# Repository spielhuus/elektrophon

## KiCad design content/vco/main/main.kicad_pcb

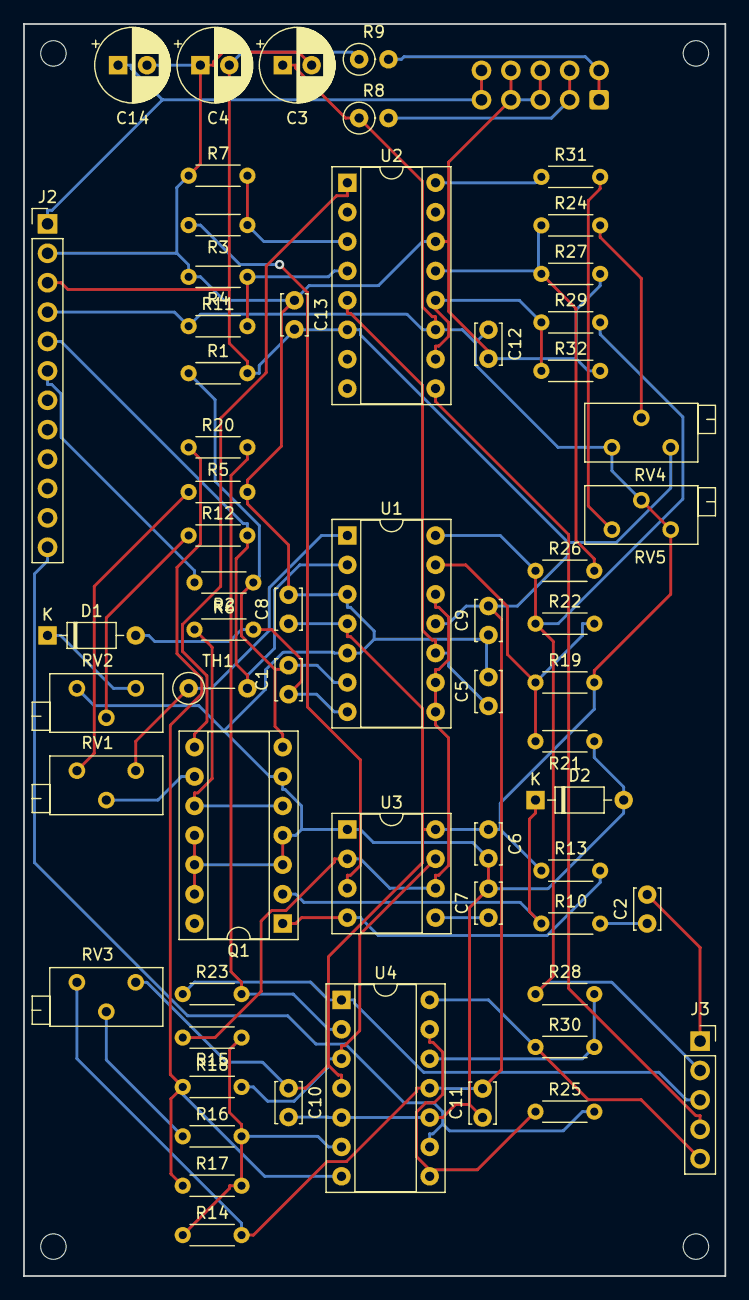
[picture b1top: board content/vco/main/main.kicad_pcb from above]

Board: 2 copper layers, 60.6 x 108.2 mm, 66 parts (1 on the bottom side), 45 nets.

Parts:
C1: 100p; C_Disc_D3.4mm_W2.1mm_P2.50mm
C2: 470p; C_Disc_D3.4mm_W2.1mm_P2.50mm
C3, C4, C14: 22u; CP_Radial_D6.3mm_P2.50mm
C5: 2200p; C_Disc_D3.4mm_W2.1mm_P2.50mm
C6, C8, C9, C10, C11, C12, C13: 0.1u; C_Disc_D3.4mm_W2.1mm_P2.50mm
C7: 0.001u; C_Disc_D3.4mm_W2.1mm_P2.50mm
D1, D2: 1N4148; D_DO-35_SOD27_P7.62mm_Horizontal
H1, H2, H3, H4: MountingHole; MountingHole_2.2mm_M2
J1: IDC Header; IDC-Header_2x05_P2.54mm_Vertical
J2: Conn_01x12_Female; PinHeader_1x12_P2.54mm_Vertical
J3: Conn_01x05_Female; PinSocket_1x05_P2.54mm_Vertical
Q1: THAT340; DIP-14_W7.62mm_Socket
R1: 1M5; R_Axial_DIN0204_L3.6mm_D1.6mm_P5.08mm_Horizontal
R2, R12, R16, R24: 1M; R_Axial_DIN0204_L3.6mm_D1.6mm_P5.08mm_Horizontal
R3, R13: 4k7; R_Axial_DIN0204_L3.6mm_D1.6mm_P5.08mm_Horizontal
R4, R7: 1k5; R_Axial_DIN0204_L3.6mm_D1.6mm_P5.08mm_Horizontal
R5, R27: 390; R_Axial_DIN0204_L3.6mm_D1.6mm_P5.08mm_Horizontal
R6: 22k; R_Axial_DIN0204_L3.6mm_D1.6mm_P5.08mm_Horizontal
R8, R9: 10; R_Axial_DIN0207_L6.3mm_D2.5mm_P2.54mm_Vertical
R10, R15, R17, R26: 100k; R_Axial_DIN0204_L3.6mm_D1.6mm_P5.08mm_Horizontal
R11, R18, R19, R20, R23: 10k; R_Axial_DIN0204_L3.6mm_D1.6mm_P5.08mm_Horizontal
R14: 150k; R_Axial_DIN0204_L3.6mm_D1.6mm_P5.08mm_Horizontal
R21, R22: 20k; R_Axial_DIN0204_L3.6mm_D1.6mm_P5.08mm_Horizontal
R25: 120k; R_Axial_DIN0204_L3.6mm_D1.6mm_P5.08mm_Horizontal
R28: 2k2; R_Axial_DIN0204_L3.6mm_D1.6mm_P5.08mm_Horizontal
R29, R31: 39k; R_Axial_DIN0204_L3.6mm_D1.6mm_P5.08mm_Horizontal
R30: 2M2; R_Axial_DIN0204_L3.6mm_D1.6mm_P5.08mm_Horizontal
R32: 300k; R_Axial_DIN0204_L3.6mm_D1.6mm_P5.08mm_Horizontal
RV1: 100; Potentiometer_Bourns_3296Z_Horizontal
RV2, RV3, RV4: 100k; Potentiometer_Bourns_3296Z_Horizontal
RV5: 25k; Potentiometer_Bourns_3296Z_Horizontal
TH1: 2k +3500ppm/°C; R_Axial_DIN0207_L6.3mm_D2.5mm_P5.08mm_Vertical
U1, U4: TL074; DIP-14_W7.62mm_Socket
U2: LM13700; DIP-16_W7.62mm_Socket
U3: TLC555xP; DIP-8_W7.62mm_Socket

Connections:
+5V: C14.1, J1.9, J1.10, J2.1
+15V: C3.1, C6.1, C8.1, C10.1, C12.1, J2.4, R8.1, R11.1, R13.1, R19.2, RV3.1, RV4.1, RV5.2, RV5.3, U1.4, U2.11, U3.8, U4.4
-15V: C4.2, C9.2, C11.2, C13.2, J2.3, R1.2, R9.1, R14.2, RV3.3, RV4.3, U1.11, U2.6, U4.11
/exp_fm: J2.5, R12.2, TH1.2, U1.2
/lin_fm: J2.6, R2.2
/net_q: R3.2, U3.3
/pulse: J3.5, R30.1, U4.14
/pwm_cv: J2.12, R25.2, U4.9
/ramp: J3.3, R23.1, U4.1
/sine: J3.4, U2.9
/sync: C2.2, J3.1
/triangle: J3.2, R22.1, R26.1, R28.1, R29.2, U1.14
GND: C3.2, C4.1, C5.2, C6.2, C7.2, C8.2, C9.1, C10.2, C11.1, C12.2, C13.1, C14.2, D2.2, J1.5, J1.6, J1.7, J1.8, J2.2, Q1.3, Q1.4, Q1.6, Q1.11, Q1.12, Q1.13, R4.2, R5.2, R7.1, R21.1, R27.2, R32.2, RV2.3, U1.3, U1.5, U2.14, U3.1, U4.5, U4.10
unnamed: C1.1, D1.2, R6.2, U1.7
unnamed: C1.2, Q1.7, R1.1, R2.1, U1.6
unnamed: C2.1, R10.2
unnamed: C5.1, U1.10, U2.5
unnamed: C7.1, U3.5
unnamed: D1.1, RV2.1
unnamed: D2.1, Q1.2, R10.1
unnamed: Q1.1, R13.2, U3.4
unnamed: Q1.8, U2.1
unnamed: Q1.9, RV1.2
unnamed: Q1.5, Q1.10, R6.1
unnamed: R3.1, R7.2, U2.3
unnamed: R5.1, RV1.3
unnamed: R4.1, R11.2, U2.4
unnamed: R12.1, RV2.2
unnamed: R14.1, R15.1, R16.2, R17.2, U4.6
unnamed: R15.2, U1.8, U1.9, U1.12, U3.2, U3.6
unnamed: R16.1, RV3.2
unnamed: R17.1, R18.1, R20.1, U4.7
unnamed: R18.2, U3.7, U4.3
unnamed: R19.1, R21.2, R22.2, U1.13
unnamed: R20.2, R23.2, U4.2
unnamed: R24.1, R26.2, R27.1, U2.13
unnamed: R24.2, RV4.2
unnamed: R25.1, U4.8, U4.13
unnamed: R28.2, R30.2, U4.12
unnamed: R29.1, R32.1, U2.10, U2.12
unnamed: R31.1, U2.16
unnamed: R31.2, RV5.1
unnamed: RV1.1, TH1.1, U1.1
VN: J1.1, J1.2, R9.2
VP: J1.3, J1.4, R8.2

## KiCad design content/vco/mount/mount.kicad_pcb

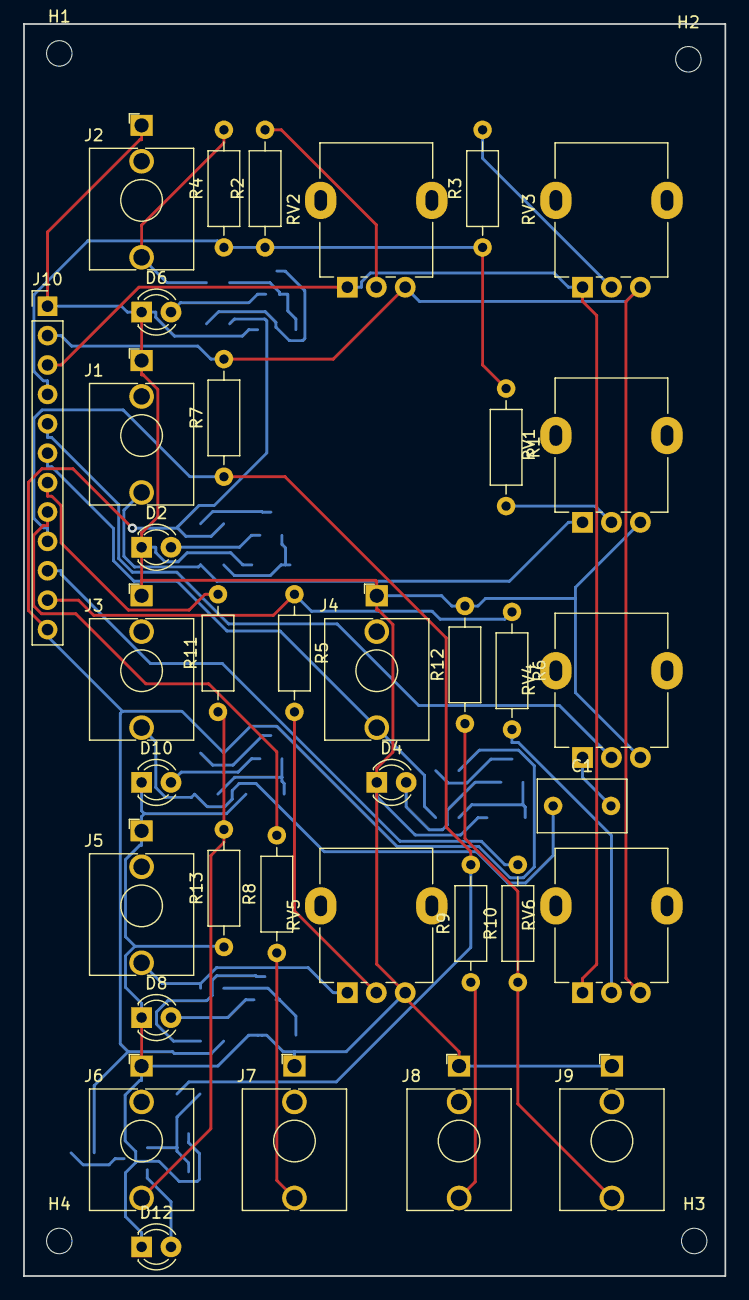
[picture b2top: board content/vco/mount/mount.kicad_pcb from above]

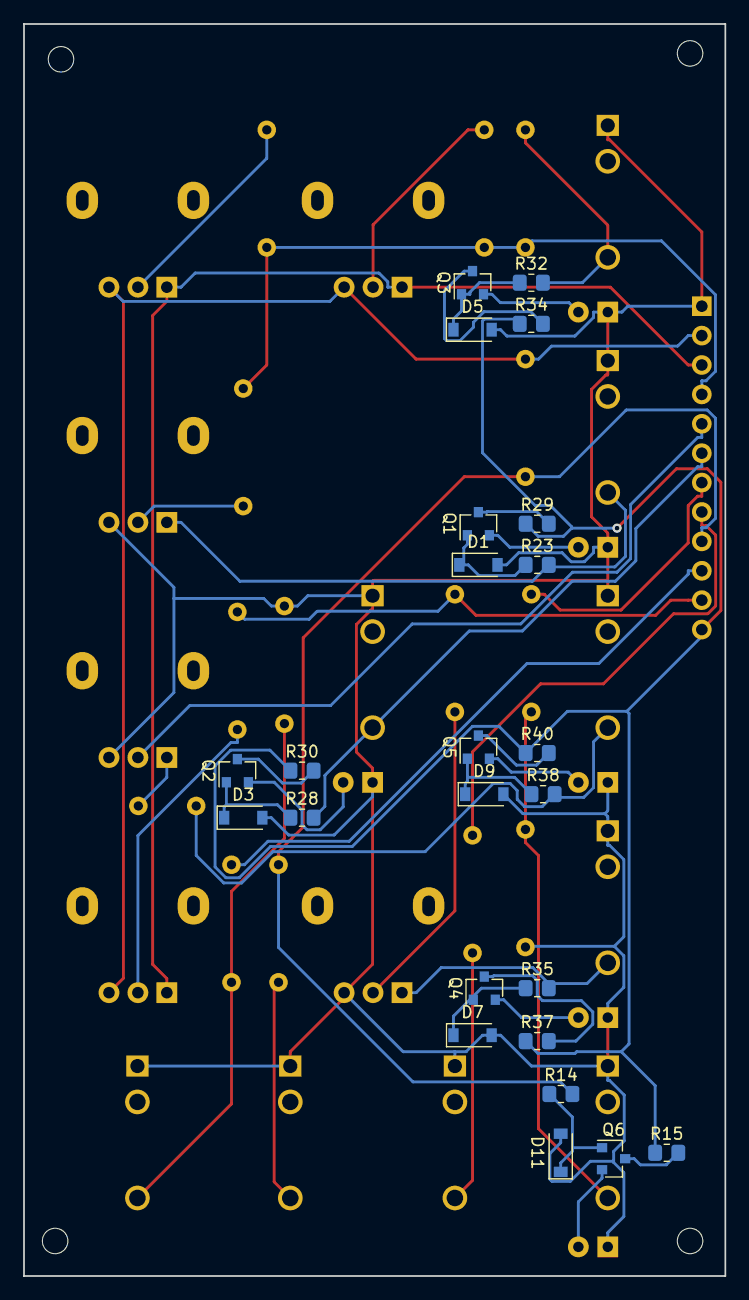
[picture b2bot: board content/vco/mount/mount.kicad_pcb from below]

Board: 2 copper layers, 60.6 x 108.2 mm, 64 parts (24 on the bottom side), 44 nets.

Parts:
C1: 0.22u; C_Disc_D7.5mm_W4.4mm_P5.00mm
D1, D3, D5, D7, D9, D11: 1N4148W; D_SOD-123
D2, D4, D6, D8, D10, D12: LED; LED_D3.0mm
H1, H2, H3, H4: MountingHole; MountingHole_2.2mm_M2
J1: exp.fm; Jack_3.5mm_WQP-PJ398SM_Vertical
J2: 1v/oct; Jack_3.5mm_WQP-PJ398SM_Vertical
J3: lin.fm; Jack_3.5mm_WQP-PJ398SM_Vertical
J4: sync; Jack_3.5mm_WQP-PJ398SM_Vertical
J5: pwm; Jack_3.5mm_WQP-PJ398SM_Vertical
J6, J7, J8, J9: AudioJack2_SwitchT; Jack_3.5mm_WQP-PJ398SM_Vertical
J10: Conn_01x12_Male; PinHeader_1x12_P2.54mm_Vertical
Q1, Q2, Q3, Q4, Q5, Q6: MMBT3904; SOT-23
R1, R2, R4, R5: 100k; R_Axial_DIN0207_L6.3mm_D2.5mm_P10.16mm_Horizontal
R3: 3M3; R_Axial_DIN0207_L6.3mm_D2.5mm_P10.16mm_Horizontal
R6: 330k; R_Axial_DIN0207_L6.3mm_D2.5mm_P10.16mm_Horizontal
R7: 5k6; R_Axial_DIN0207_L6.3mm_D2.5mm_P10.16mm_Horizontal
R8, R9: 1k; R_Axial_DIN0207_L6.3mm_D2.5mm_P10.16mm_Horizontal
R10: 3k; R_Axial_DIN0207_L6.3mm_D2.5mm_P10.16mm_Horizontal
R11, R13: 2k; R_Axial_DIN0207_L6.3mm_D2.5mm_P10.16mm_Horizontal
R12: 1k8; R_Axial_DIN0207_L6.3mm_D2.5mm_P10.16mm_Horizontal
R14, R23, R28, R32, R35, R38: 100k; R_0805_2012Metric_Pad1.20x1.40mm_HandSolder
R15, R30, R37: 5k; R_0805_2012Metric_Pad1.20x1.40mm_HandSolder
R29, R34, R40: 5.1k; R_0805_2012Metric_Pad1.20x1.40mm_HandSolder
RV1, RV2, RV3, RV4, RV5, RV6: 100k; Potentiometer_Alpha_RD901F-40-00D_Single_Vertical

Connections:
+5V: J10.12, R15.1, R29.1, R30.1, R34.1, R37.1, R40.1
+15V: J10.3, RV2.1, RV3.1, RV6.1
-15V: J10.2, R7.2, RV2.3, RV3.3, RV6.3
/exp.fm: J1.T, R23.2, RV1.1
/exp_fm: J10.4, R1.1, R2.1, R3.1, R4.1
/lin.fm: C1.1, J3.T, R38.2
/lin_fm: J10.5, RV4.2
/pulse: J10.10, R10.2
/pwm: J5.T, R35.2, RV5.1
/pwm_cv: J10.11, R5.1, R6.1
/ramp: J10.8, R8.2
/sine: J10.9, R7.1, R9.2, R14.2
/sync: J4.T, J10.6, R28.2
/triangle: J10.7, R11.2
/v_oct: J2.T, R4.2, R32.2
GND: D1.2, D2.1, D3.2, D4.1, D5.2, D6.1, D7.2, D8.1, D9.2, D10.1, D11.2, D12.1, J1.S, J2.S, J3.S, J4.S, J5.S, J6.S, J7.S, J8.S, J9.S, J10.1, R12.2, R13.1, RV1.3, RV4.3, RV5.3
unnamed: C1.2, RV4.1
unnamed: D1.1, Q1.1, R23.1
unnamed: D2.2, Q1.2
unnamed: D3.1, Q2.1, R28.1
unnamed: D4.2, Q2.2
unnamed: D5.1, Q3.1, R32.1
unnamed: D6.2, Q3.2
unnamed: D7.1, Q4.1, R35.1
unnamed: D8.2, Q4.2
unnamed: D9.1, Q5.1, R38.1
unnamed: D10.2, Q5.2
unnamed: D11.1, Q6.1, R14.1
unnamed: D12.2, Q6.2
unnamed: J6.T, R11.1, R13.2
unnamed: J7.T, R8.1
unnamed: J8.T, R9.1
unnamed: J9.T, R10.1, R12.1
unnamed: Q1.3, R29.2
unnamed: Q2.3, R30.2
unnamed: Q3.3, R34.2
unnamed: Q4.3, R37.2
unnamed: Q5.3, R40.2
unnamed: Q6.3, R15.2
unnamed: R1.2, RV1.2
unnamed: R2.2, RV2.2
unnamed: R3.2, RV3.2
unnamed: R5.2, RV5.2
unnamed: R6.2, RV6.2

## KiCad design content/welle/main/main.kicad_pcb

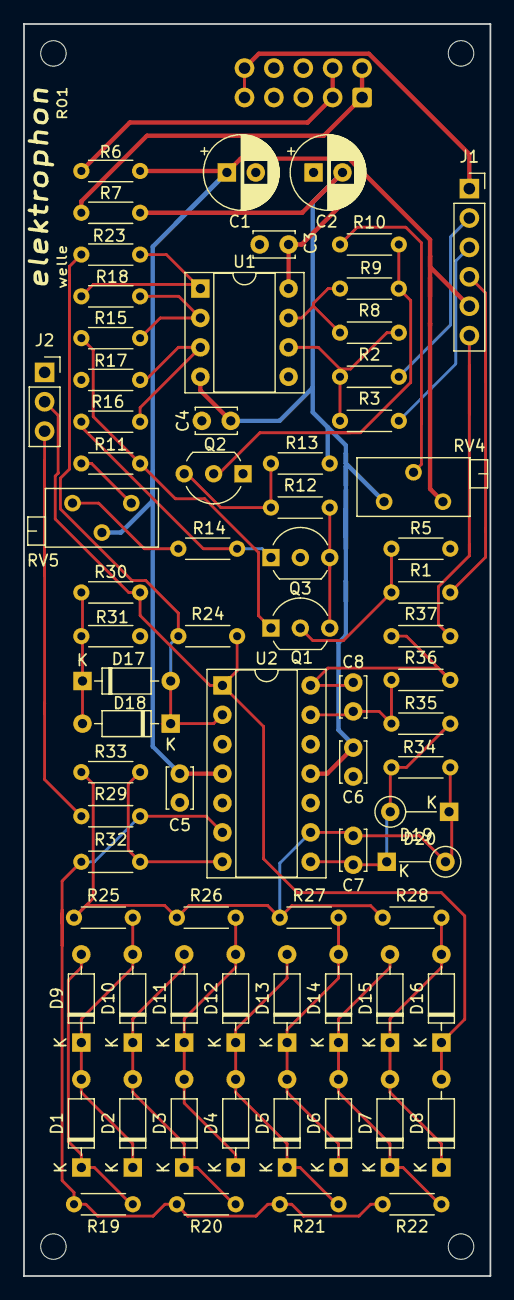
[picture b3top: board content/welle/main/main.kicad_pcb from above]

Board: 2 copper layers, 40.3 x 108.2 mm, 78 parts (1 on the bottom side), 42 nets.

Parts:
C1, C2: 22u; CP_Radial_D6.3mm_P2.50mm
C3, C4, C5, C6: 0.1u; C_Disc_D3.4mm_W2.1mm_P2.50mm
C7, C8: 10p*; C_Disc_D3.4mm_W2.1mm_P2.50mm
D1, D2, D3, D4, D5, D6, D7, D8, D9, D10, D11, D12, D13, D14, D15, D16, D17, D18: D; D_DO-35_SOD27_P7.62mm_Horizontal
D19, D20: D; D_DO-35_SOD27_P5.08mm_Vertical_KathodeUp
H1, H2, H3, H4: MountingHole; MountingHole_2.2mm_M2
J1: Conn_01x06_Female; PinSocket_1x06_P2.54mm_Vertical
J2: Conn_01x03_Female; PinSocket_1x03_P2.54mm_Vertical
J4: 10 Pos; IDC-Header_2x05_P2.54mm_Vertical
Q1, Q2, Q3: BC547; TO-92_Inline_Wide
R1, R3, R8, R17, R18, R23, R24: 100k; R_Axial_DIN0204_L3.6mm_D1.6mm_P5.08mm_Horizontal
R2: 68k; R_Axial_DIN0204_L3.6mm_D1.6mm_P5.08mm_Horizontal
R5: 680; R_Axial_DIN0204_L3.6mm_D1.6mm_P5.08mm_Horizontal
R6, R7: 10; R_Axial_DIN0204_L3.6mm_D1.6mm_P5.08mm_Horizontal
R9, R10: 22k; R_Axial_DIN0204_L3.6mm_D1.6mm_P5.08mm_Horizontal
R11, R13, R14, R19, R20, R21, R22, R25, R26, R27, R28: 15k; R_Axial_DIN0204_L3.6mm_D1.6mm_P5.08mm_Horizontal
R12, R30: 33k; R_Axial_DIN0204_L3.6mm_D1.6mm_P5.08mm_Horizontal
R15, R16: 10k; R_Axial_DIN0204_L3.6mm_D1.6mm_P5.08mm_Horizontal
R29: 27k; R_Axial_DIN0204_L3.6mm_D1.6mm_P5.08mm_Horizontal
R31: 2k7; R_Axial_DIN0204_L3.6mm_D1.6mm_P5.08mm_Horizontal
R32, R33: 5k6; R_Axial_DIN0204_L3.6mm_D1.6mm_P5.08mm_Horizontal
R34, R36: 56k; R_Axial_DIN0204_L3.6mm_D1.6mm_P5.08mm_Horizontal
R35: 6k8; R_Axial_DIN0204_L3.6mm_D1.6mm_P5.08mm_Horizontal
R37: 470; R_Axial_DIN0204_L3.6mm_D1.6mm_P5.08mm_Horizontal
RV4: 50k; Potentiometer_Bourns_3296Z_Horizontal
RV5: 1k; Potentiometer_Bourns_3296Z_Horizontal
U1: TL072; DIP-8_W7.62mm_Socket
U2: TL074; DIP-14_W7.62mm_Socket

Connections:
+5V: J1.1, J4.9, J4.10
+15V: C1.1, C3.1, C5.1, J1.5, R6.1, RV4.3, RV5.2, U1.8, U2.4
-15V: C2.2, C4.2, C6.2, R7.1, R13.1, RV4.1, U1.4, U2.11
/control: J1.2, R2.2
/input: J1.4, R1.2
/out: J1.6, R37.2
/range: J1.3, R3.2
/shape_a: D8.2, D16.1, J2.2, R24.2, R30.1, U2.1
/shape_b: J2.3, R29.1
GND: C1.2, C2.1, C3.2, C4.1, C5.2, C6.1, J2.1, J4.5, J4.6, J4.7, J4.8, Q2.1, Q3.2, R5.1, R17.1, R31.1, U1.5, U2.3, U2.5, U2.10, U2.12
unnamed: C7.1, D19.1, D20.2, R34.2, R35.1, U2.8
unnamed: C7.2, D19.2, D20.1, R25.1, R26.1, R27.1, R28.1, R33.2, R34.1, U2.9
unnamed: C8.1, R36.2, R37.1, U2.14
unnamed: C8.2, R35.2, R36.1, U2.13
unnamed: D1.1, D9.2, R19.1
unnamed: D1.2, D2.1, D9.1, D10.2, R25.2
unnamed: D2.2, D3.1, D10.1, D11.2, R20.1
unnamed: D3.2, D4.1, D11.1, D12.2, R26.2
unnamed: D4.2, D5.1, D12.1, D13.2, R21.1
unnamed: D5.2, D6.1, D13.1, D14.2, R27.2
unnamed: D6.2, D7.1, D14.1, D15.2, R22.1
unnamed: D7.2, D8.1, D15.1, D16.2, R28.2
unnamed: D17.1, D18.2, R30.2, R31.2
unnamed: D17.2, D18.1, R23.2, R24.1, U2.2
unnamed: Q1.1, R11.1, R15.2
unnamed: Q1.2, R1.1, R5.2
unnamed: Q1.3, Q3.3, R12.2
unnamed: Q2.2, R9.1, R10.2
unnamed: Q2.3, R12.1, R13.2
unnamed: Q3.1, R14.1, R16.2
unnamed: R2.1, R3.1, R8.2, U1.6
unnamed: R8.1, R9.2, U1.7
unnamed: R10.1, RV4.2
unnamed: R11.2, RV5.1
unnamed: R14.2, RV5.3
unnamed: R15.1, R18.1, U1.2
unnamed: R16.1, R17.2, U1.3
unnamed: R18.2, R23.1, U1.1
unnamed: R19.2, R20.2, R21.2, R22.2, R29.2, R32.1, U2.6
unnamed: R32.2, R33.1, U2.7
VN: J4.1, J4.2, R7.2
VP: J4.3, J4.4, R6.2

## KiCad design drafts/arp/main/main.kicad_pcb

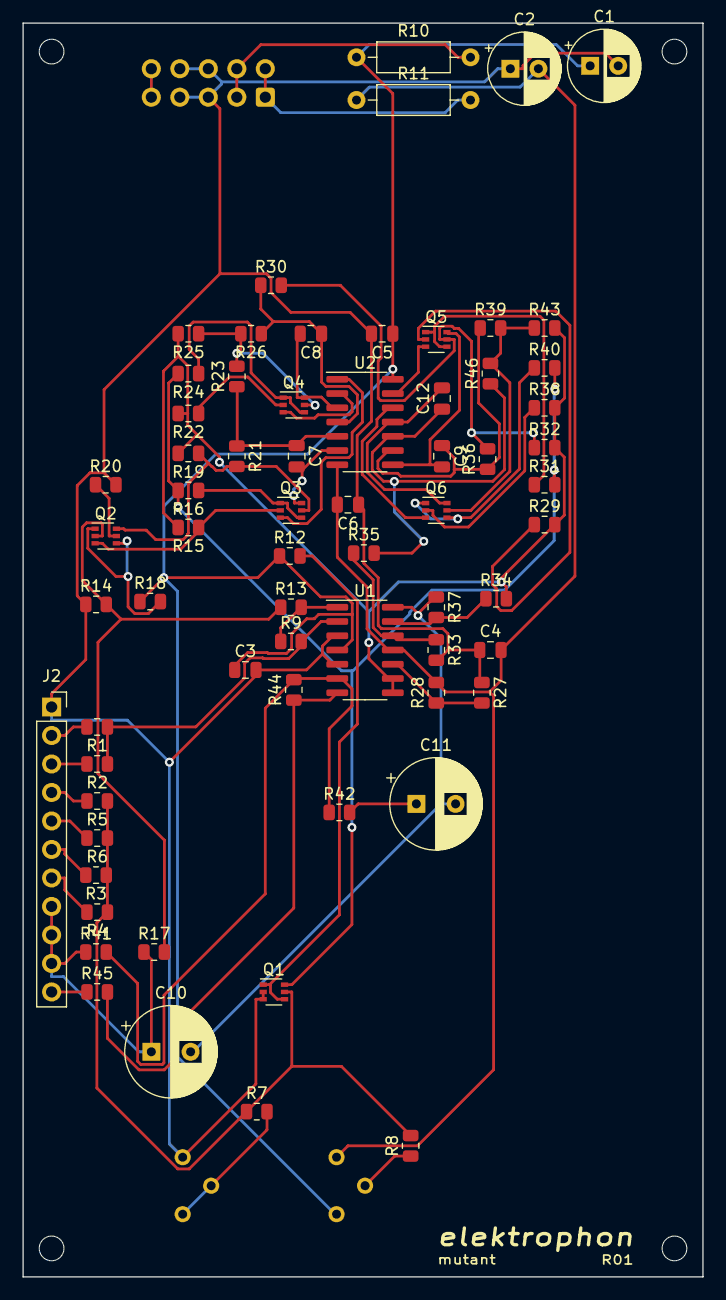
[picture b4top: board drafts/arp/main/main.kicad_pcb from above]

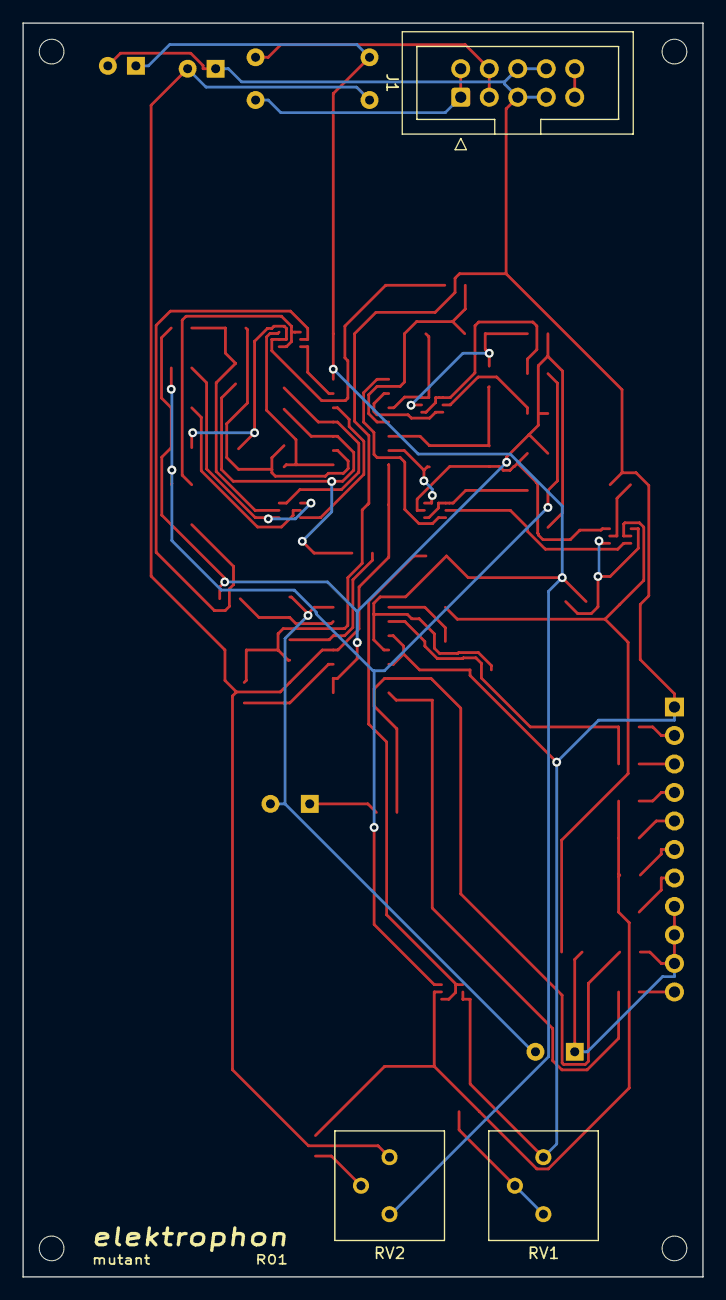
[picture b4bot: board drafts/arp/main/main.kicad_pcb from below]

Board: 2 copper layers, 60.6 x 111.8 mm, 74 parts (3 on the bottom side), 56 nets.

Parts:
C1, C2: 22u; CP_Radial_D6.3mm_P2.50mm
C3, C4, C5, C6: 0.1u; C_0805_2012Metric
C7, C8, C9, C12: 470p; C_0805_2012Metric
C10, C11: 22u; CP_Radial_D8.0mm_P3.50mm
J1: IDC Header; IDC-Header_2x05_P2.54mm_Vertical
J2: Conn_01x11_Female; PinSocket_1x11_P2.54mm_Vertical
Q1, Q2, Q3, Q4, Q5, Q6: MMDT3906; SOT-363_SC-70-6
R1, R2, R4, R5, R6, R8, R9, R13, R33: 100k; R_0805_2012Metric
R3: 150k; R_0805_2012Metric
R7, R14, R16, R24, R31, R40, R45: 1k; R_0805_2012Metric
R10, R11: 10; R_Axial_DIN0207_L6.3mm_D2.5mm_P10.16mm_Horizontal
R12, R21, R23, R26, R27, R28, R30, R34, R35, R36, R37, R39, R46: 10k; R_0805_2012Metric
R15, R19, R20, R22, R25, R29, R32, R38, R43: 220; R_0805_2012Metric
R17: 15k; R_0805_2012Metric
R18: 33k; R_0805_2012Metric
R41: 22k; R_0805_2012Metric
R42, R44: 56k; R_0805_2012Metric
REF1, REF2, REF3, REF4: MountingHole_2.2mm_M2
RV1: 2.2k; Potentiometer_Bourns_3386P_Vertical
RV2: 47k; Potentiometer_Bourns_3386P_Vertical
U1: TL074; SOIC-14_3.9x8.7mm_P1.27mm
U2: LM3900; SOIC-14_3.9x8.7mm_P1.27mm

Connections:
+5V: J1.9, J1.10
+15V: C1.1, C3.1, C5.1, R10.1, R12.1, R18.1, RV2.3, U1.4, U2.14
-15V: C2.2, C4.2, C6.2, R11.1, R28.2, RV2.1, U1.11, U2.7
CV1: J2.4, R5.2
CV2: J2.5, R6.2
FREQ: J2.6, R3.2
GND: C1.2, C2.1, C3.2, C4.1, C5.2, C6.1, J1.5, J1.6, J1.7, J1.8, J2.1, Q1.2, Q1.3, R14.1, R20.2, R27.1, R33.2, RV1.1, U1.3, U1.5
IN1: J2.2, R1.2
IN2: J2.3, R2.2
unnamed: C7.1, R21.1, R23.1, U2.5
unnamed: C7.2, Q3.6, U2.6
unnamed: C8.1, R26.1, R30.1, U2.4
unnamed: C8.2, Q4.6, U2.3
unnamed: C9.1, R36.1, R39.1, U2.9
unnamed: C9.2, Q5.6, U2.8
unnamed: C10.2, C11.2, R37.1, U1.14
unnamed: C11.1, R42.2
unnamed: C12.1, R35.2, R46.1, U2.10
unnamed: C12.2, Q6.6, U2.11
unnamed: Q1.1, Q1.4, R12.2
unnamed: Q1.5, R3.1, R4.1, R5.1, R6.1, R7.1, R8.2
unnamed: Q1.6, R16.2, R24.2, R31.2, R40.2
unnamed: Q2.1, Q2.4, R18.2
unnamed: Q2.2, R13.1, R14.2, R17.2
unnamed: Q2.3, Q3.2, R15.1
unnamed: Q2.5, R20.1
unnamed: Q2.6, Q3.5, R19.1, R21.2
unnamed: Q3.1, Q3.4, R16.1
unnamed: Q3.3, U2.1
unnamed: Q4.1, Q4.4, R24.1
unnamed: Q4.2, R22.1
unnamed: Q4.3, U2.2
unnamed: Q4.5, R23.2, R25.1, R26.2
unnamed: Q5.1, Q5.4, R31.1
unnamed: Q5.2, R29.1
unnamed: Q5.3, U2.13
unnamed: Q5.5, R30.2, R32.1, R36.2
unnamed: Q6.1, Q6.4, R40.1
unnamed: Q6.2, R38.1
unnamed: Q6.3, U2.12
unnamed: Q6.5, R39.2, R43.1, R46.2
unnamed: R1.1, R2.1, R9.2, U1.2
unnamed: R7.2, RV1.2, RV1.3
unnamed: R8.1, RV2.2
unnamed: R9.1, R13.2, U1.1
unnamed: R15.2, R19.2, R22.2, R25.2, R29.2, R32.2, R34.2, R38.2, R43.2, U1.8, U1.9
unnamed: R27.2, R28.1, U1.10
unnamed: R33.1, R35.1, U1.12
unnamed: R34.1, R37.2, U1.13
unnamed: R41.2, R42.1, R44.2, U1.6
unnamed: R44.1, R45.2, U1.7
OUT: J2.11, R45.1
RES_A: C10.1, J2.8, J2.9, J2.10, R17.1, R41.1
VN: J1.1, J1.2, R11.2
VP: J1.3, J1.4, R10.2
V_OCT: J2.7, R4.2

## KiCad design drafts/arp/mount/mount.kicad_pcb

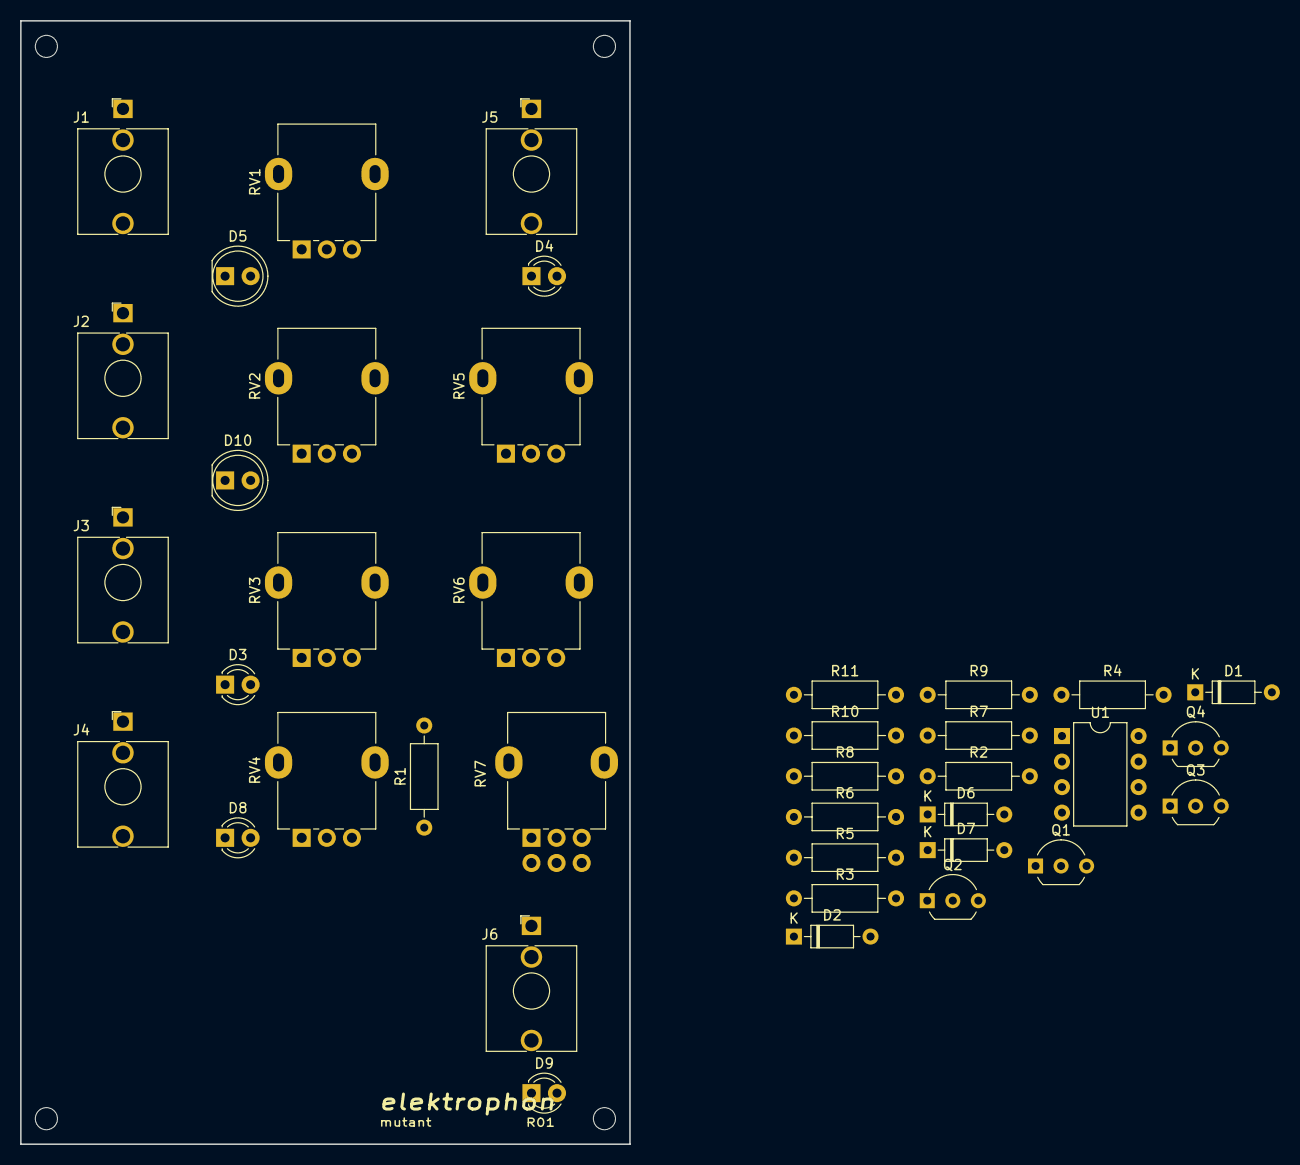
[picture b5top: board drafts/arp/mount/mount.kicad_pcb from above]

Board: 2 copper layers, 60.6 x 111.8 mm, 43 parts (0 on the bottom side), 31 nets, no tracks yet.

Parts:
D1, D2, D6, D7: 1N4148; D_DO-35_SOD27_P7.62mm_Horizontal
D3, D4, D8, D9: WP710A10L; LED_D3.0mm
D5, D10: LED_Dual_2pin; LED_D5.0mm
J1: CV1; Jack_3.5mm_WQP-PJ398SM_Vertical
J2: CV2; Jack_3.5mm_WQP-PJ398SM_Vertical
J3: IN1; Jack_3.5mm_WQP-PJ398SM_Vertical
J4: IN2; Jack_3.5mm_WQP-PJ398SM_Vertical
J5: V/OCT; Jack_3.5mm_WQP-PJ398SM_Vertical
J6: OUT; Jack_3.5mm_WQP-PJ398SM_Vertical
Q1, Q2, Q3, Q4: BC550; TO-92_Inline_Wide
R1: 1k; R_Axial_DIN0207_L6.3mm_D2.5mm_P10.16mm_Horizontal
R2, R3, R7, R8: 100k; R_Axial_DIN0207_L6.3mm_D2.5mm_P10.16mm_Horizontal
R4, R5, R9, R10: 5.6k; R_Axial_DIN0207_L6.3mm_D2.5mm_P10.16mm_Horizontal
R6, R11: 490; R_Axial_DIN0207_L6.3mm_D2.5mm_P10.16mm_Horizontal
REF1, REF2, REF3, REF4: MountingHole_2.2mm_M2
RV1, RV2, RV3, RV4: 47k; Potentiometer_Alpha_RD901F-40-00D_Single_Vertical
RV5: 20k; Potentiometer_Alpha_RD901F-40-00D_Single_Vertical
RV6: 50k (log); Potentiometer_Alpha_RD901F-40-00D_Single_Vertical
RV7: 100k; Potentiometer_Alpha_RD902F-40-00D_Dual_Vertical
U1: TL072; DIP-8_W7.62mm

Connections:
+5V: R4.2, R5.2, R9.2, R10.2
+15V: RV5.3, U1.8
CV: RV1.2, U1.3
CV2: RV2.2, U1.5
GND: D1.2, D2.2, D3.1, D4.1, D6.2, D7.2, D8.1, D9.1, J1.S, J2.S, J3.S, J4.S, J5.S, J6.S, R6.1, R11.1, RV1.1, RV2.1, RV3.1, RV4.1, RV5.1, RV6.1, RV7.3, RV7.6
IN_1: R2.2, RV3.2
IN_2: R7.2, RV4.2
unnamed: D1.1, Q1.2, R2.1
unnamed: D2.1, Q2.2, R3.1
unnamed: D3.2, Q1.3
unnamed: D4.2, Q2.3
unnamed: D5.1, R6.2
unnamed: D5.2, U1.1, U1.2
unnamed: D6.1, Q3.2, R7.1
unnamed: D7.1, Q4.2, R8.1
unnamed: D8.2, Q3.3
unnamed: D9.2, Q4.3
unnamed: D10.1, R11.2
unnamed: D10.2, U1.6, U1.7
unnamed: J1.T, RV1.3
unnamed: J2.T, RV2.3
unnamed: J3.T, RV3.3
unnamed: J4.T, RV4.3
unnamed: J6.T, R1.1
unnamed: Q1.1, R4.1
unnamed: Q2.1, R5.1
unnamed: Q3.1, R9.1
unnamed: Q4.1, R10.1
OUT: R1.2, R8.2
RES_B: RV7.1, RV7.4
V_OCT: J5.T, R3.2

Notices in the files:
content/vco/main/main.kicad_pcb:
License CC BY 4.0 - Attribution 4.0 International
